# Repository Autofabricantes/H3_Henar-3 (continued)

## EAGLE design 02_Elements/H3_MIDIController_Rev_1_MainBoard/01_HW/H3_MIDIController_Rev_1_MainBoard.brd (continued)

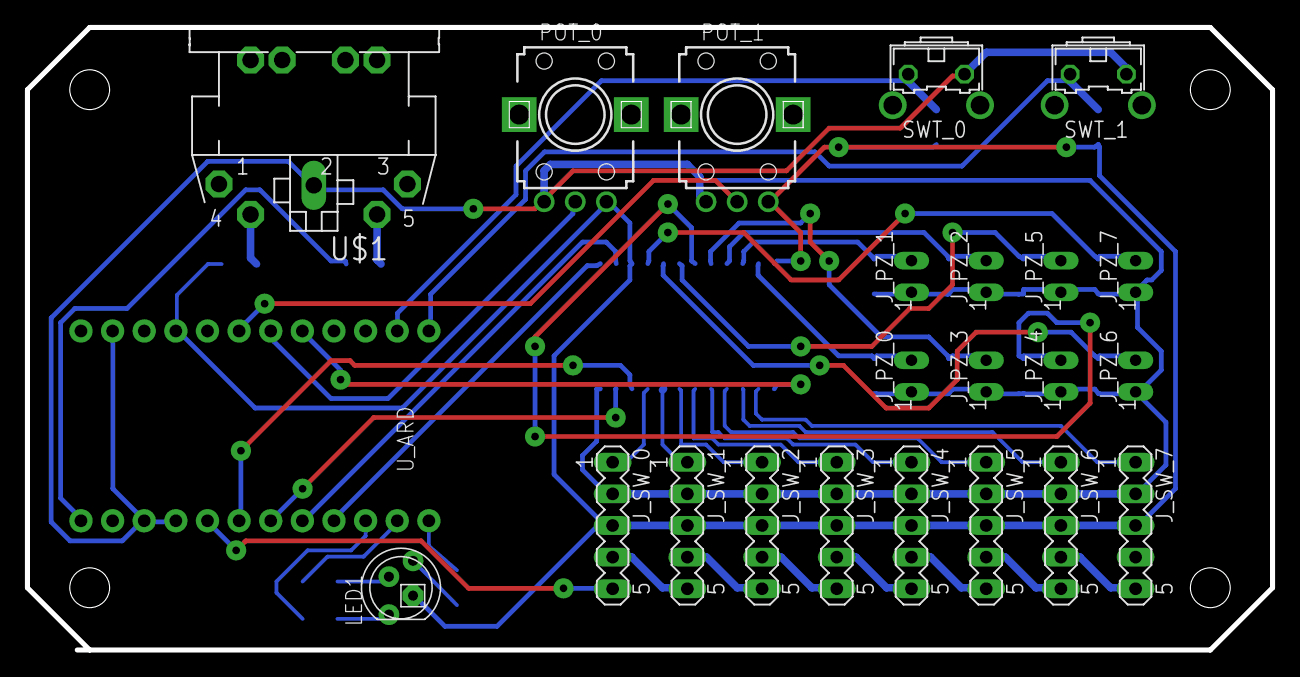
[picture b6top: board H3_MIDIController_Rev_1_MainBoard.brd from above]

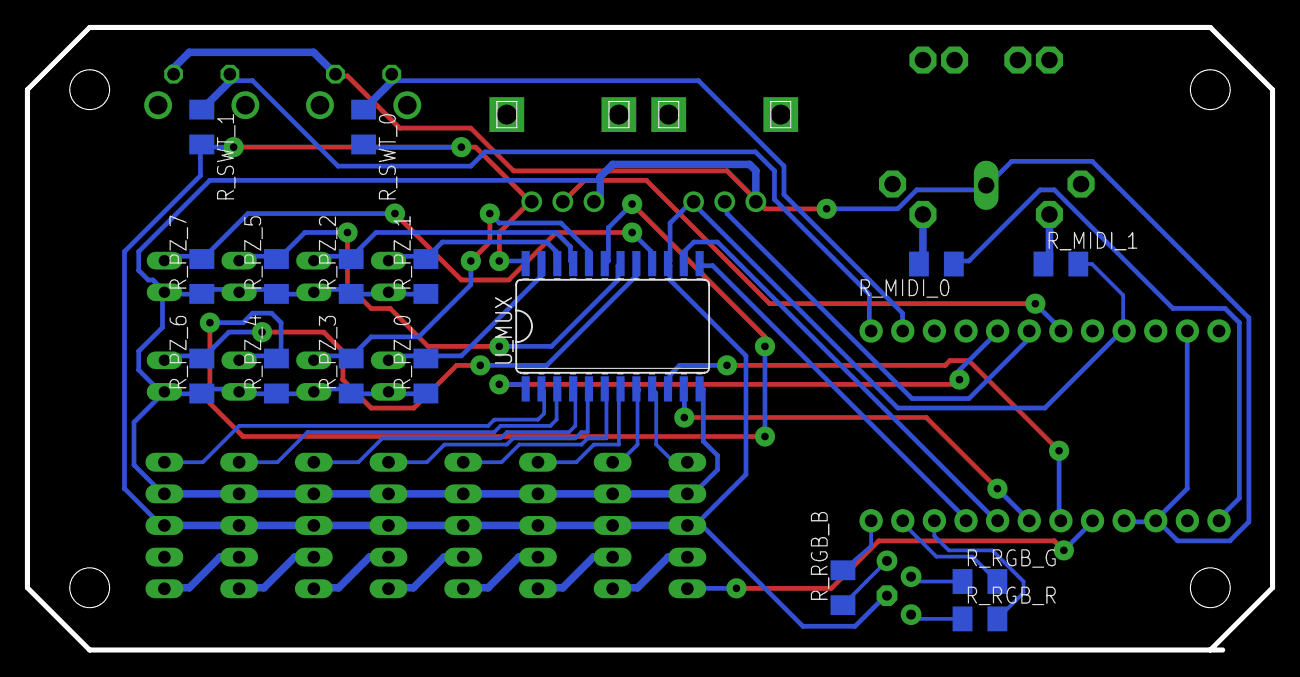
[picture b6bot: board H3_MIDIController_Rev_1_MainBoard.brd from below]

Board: 2 copper layers, 100.0 x 50.0 mm, 39 parts (16 on the bottom side), 44 nets.

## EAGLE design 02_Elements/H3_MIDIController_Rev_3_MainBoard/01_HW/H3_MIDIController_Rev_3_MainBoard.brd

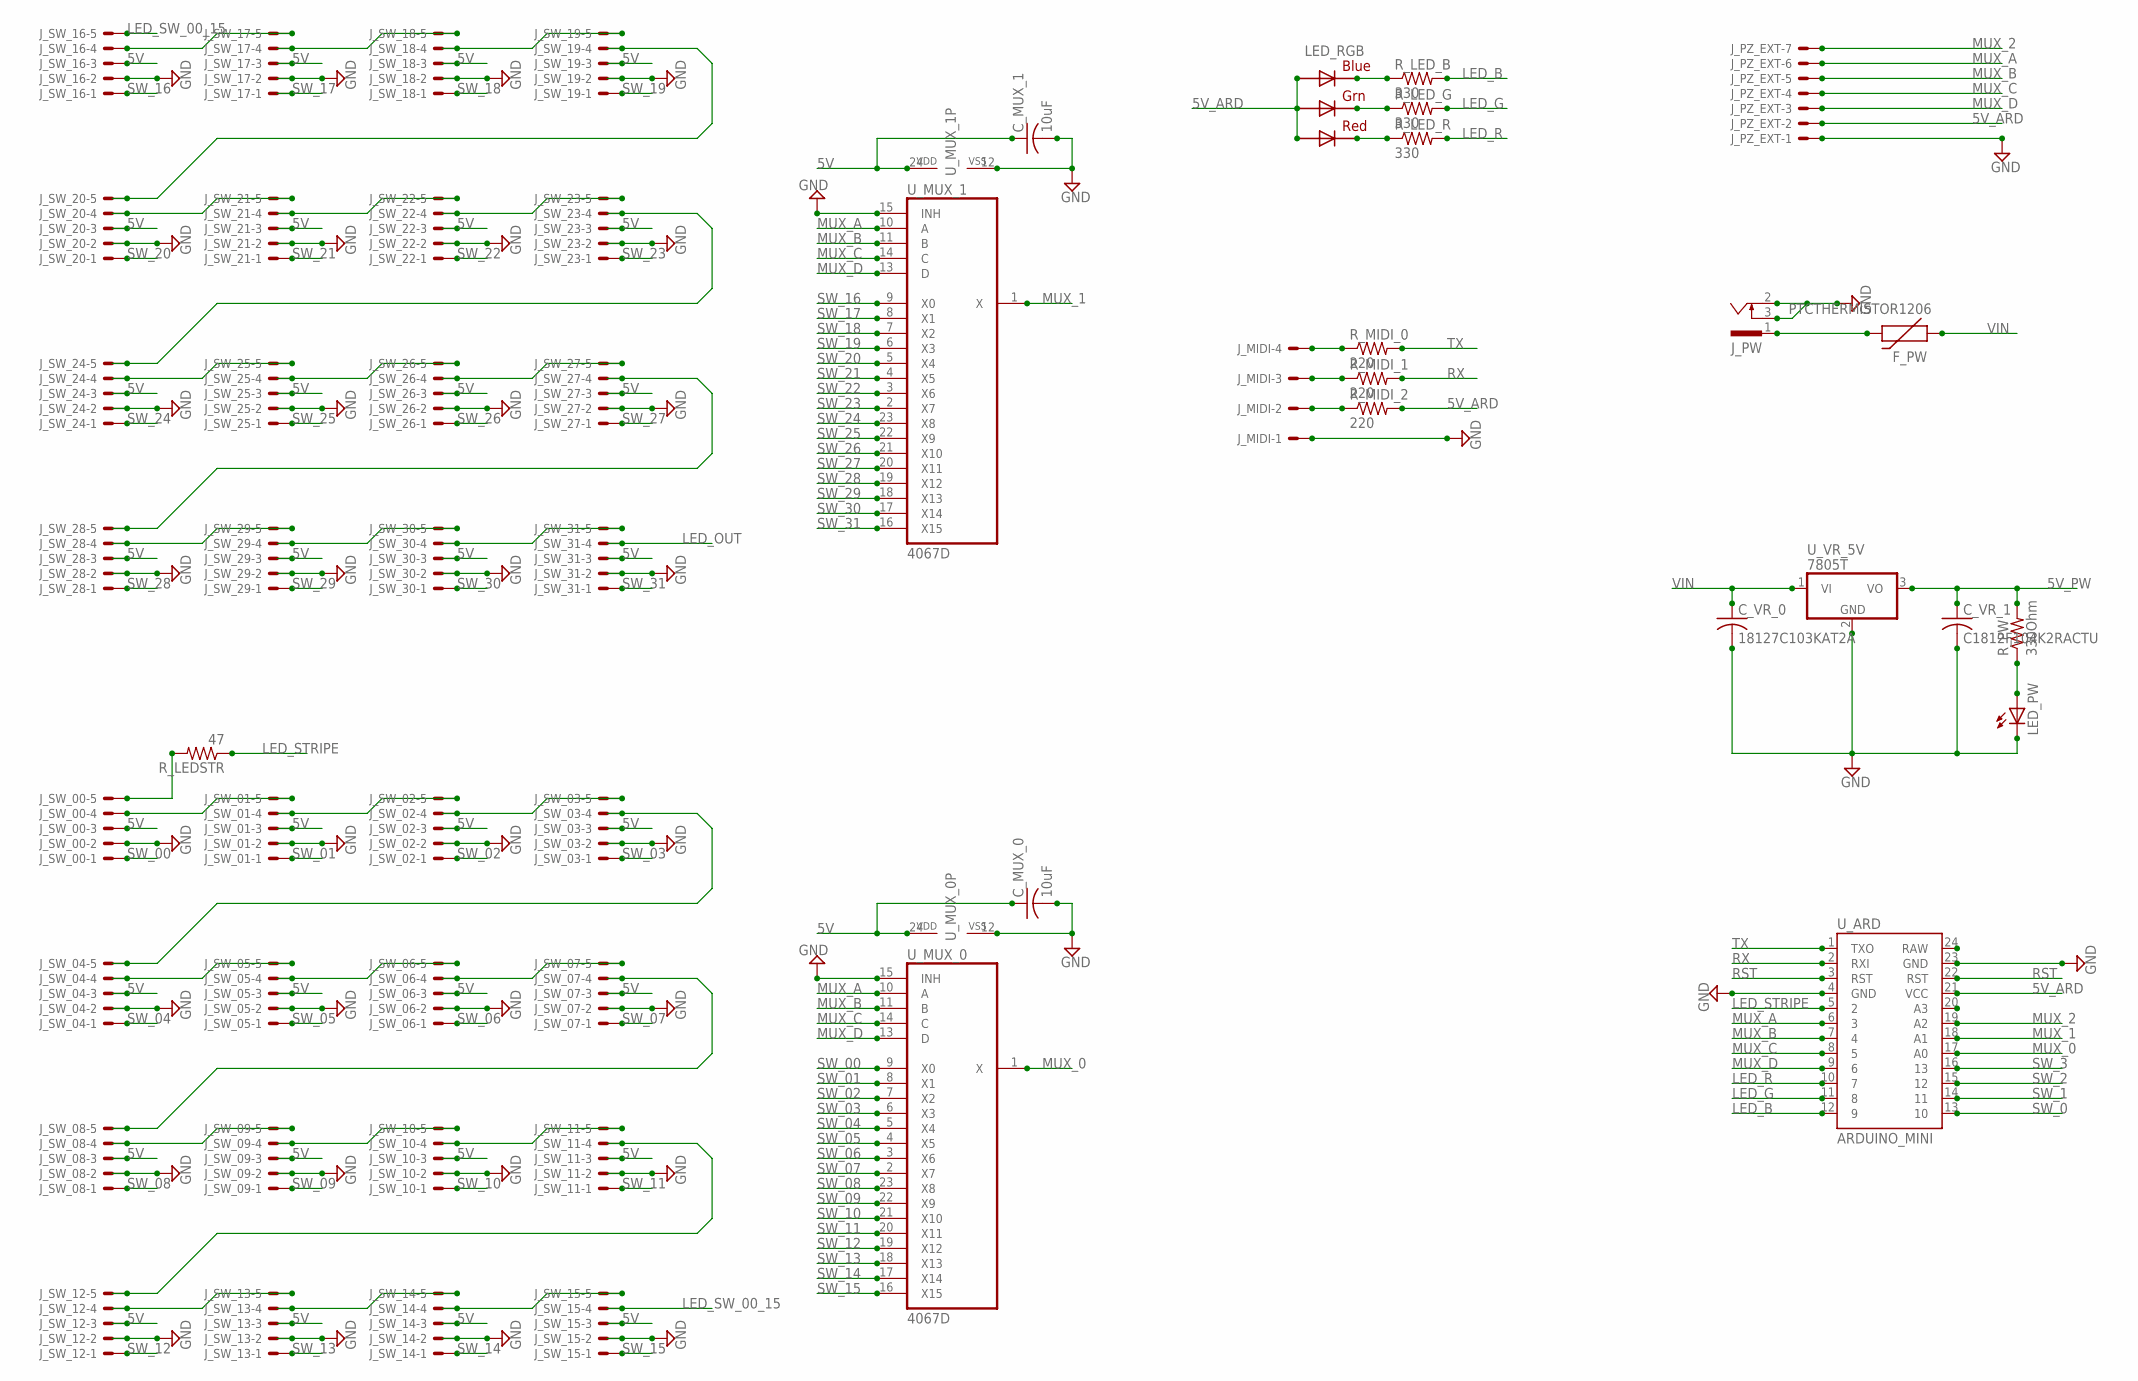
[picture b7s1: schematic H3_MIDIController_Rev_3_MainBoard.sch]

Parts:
C_MUX_0, C_MUX_1: 10uF; C1206K
C_VR_0: 18127C103KAT2A; C1812K
C_VR_1: C1812F104K2RACTU; C1812K
F_PW: PTCTHERMISTOR1206; PTC-1206
J_MIDI: 22-05-7048-04; 7395-04
J_PW: SCD-014A; SCD-014-A
J_PZ_EXT: 22-05-7078-07; 7395-07
J_SW_00, J_SW_01, J_SW_02, J_SW_03, J_SW_04, J_SW_05, J_SW_06, J_SW_07, J_SW_08, J_SW_09, J_SW_10, J_SW_11, J_SW_12, J_SW_13, J_SW_14, J_SW_15, J_SW_16, J_SW_17, J_SW_18, J_SW_19, J_SW_20, J_SW_21, J_SW_22, J_SW_23, J_SW_24, J_SW_25, J_SW_26, J_SW_27, J_SW_28, J_SW_29, J_SW_30, J_SW_31: 22-05-7058-05; 7395-05
LED_PW: LEDSMT1206; 1206
LED_RGB: RGBLED5050
R_LEDSTR: 47; M1206
R_LED_B: 330; M1206
R_LED_G: 330; M1206
R_LED_R: 330; M1206
R_MIDI_0, R_MIDI_1, R_MIDI_2: 220; M1206
R_PW: 330Ohm; M1206
U_ARD: ARDUINO_MINI
U_MUX_0, U_MUX_1: 4067D; SO24W
U_VR_5V: 7805T; TO220H

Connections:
5V: C_MUX_0.1, C_MUX_1.1, J_SW_00.3, J_SW_01.3, J_SW_02.3, J_SW_03.3, J_SW_04.3, J_SW_05.3, J_SW_06.3, J_SW_07.3, J_SW_08.3, J_SW_09.3, J_SW_10.3, J_SW_11.3, J_SW_12.3, J_SW_13.3, J_SW_14.3, J_SW_15.3, J_SW_16.3, J_SW_17.3, J_SW_18.3, J_SW_19.3, J_SW_20.3, J_SW_21.3, J_SW_22.3, J_SW_23.3, J_SW_24.3, J_SW_25.3, J_SW_26.3, J_SW_27.3, J_SW_28.3, J_SW_29.3, J_SW_30.3, J_SW_31.3, U_MUX_0.24 (VDD), U_MUX_1.24 (VDD)
5V_ARD: J_PZ_EXT.2, LED_RGB.1 (GREEN_A), LED_RGB.2 (RED_A), LED_RGB.3 (BLUE_A), R_MIDI_2.2, U_ARD.21 (VCC)
5V_PW: C_VR_1.1, R_PW.2, U_VR_5V.3 (VO)
GND: C_MUX_0.2, C_MUX_1.2, C_VR_0.2, C_VR_1.2, J_MIDI.1, J_PW.2, J_PW.3, J_PZ_EXT.1, J_SW_00.2, J_SW_01.2, J_SW_02.2, J_SW_03.2, J_SW_04.2, J_SW_05.2, J_SW_06.2, J_SW_07.2, J_SW_08.2, J_SW_09.2, J_SW_10.2, J_SW_11.2, J_SW_12.2, J_SW_13.2, J_SW_14.2, J_SW_15.2, J_SW_16.2, J_SW_17.2, J_SW_18.2, J_SW_19.2, J_SW_20.2, J_SW_21.2, J_SW_22.2, J_SW_23.2, J_SW_24.2, J_SW_25.2, J_SW_26.2, J_SW_27.2, J_SW_28.2, J_SW_29.2, J_SW_30.2, J_SW_31.2, LED_PW.C, U_ARD.4 (GND), U_ARD.23 (GND), U_MUX_0.12 (VSS), U_MUX_0.15 (INH), U_MUX_1.12 (VSS), U_MUX_1.15 (INH), U_VR_5V.2 (GND)
LED_B: R_LED_B.2, U_ARD.12 (9)
LED_G: R_LED_G.2, U_ARD.11 (8)
LED_IN1: J_SW_00.4, J_SW_01.5
LED_IN2: J_SW_01.4, J_SW_02.5
LED_IN3: J_SW_02.4, J_SW_03.5
LED_IN4: J_SW_03.4, J_SW_04.5
LED_IN5: J_SW_04.4, J_SW_05.5
LED_IN6: J_SW_05.4, J_SW_06.5
LED_IN7: J_SW_07.4, J_SW_08.5
LED_IN8: J_SW_08.4, J_SW_09.5
LED_IN9: J_SW_09.4, J_SW_10.5
LED_IN10: J_SW_10.4, J_SW_11.5
LED_IN11: J_SW_11.4, J_SW_12.5
LED_IN12: J_SW_12.4, J_SW_13.5
LED_IN13: J_SW_13.4, J_SW_14.5
LED_IN14: J_SW_14.4, J_SW_15.5
LED_IN15: J_SW_16.4, J_SW_17.5
LED_IN16: J_SW_17.4, J_SW_18.5
LED_IN17: J_SW_18.4, J_SW_19.5
LED_IN18: J_SW_19.4, J_SW_20.5
LED_IN19: J_SW_20.4, J_SW_21.5
LED_IN20: J_SW_21.4, J_SW_22.5
LED_IN21: J_SW_23.4, J_SW_24.5
LED_IN22: J_SW_24.4, J_SW_25.5
LED_IN23: J_SW_25.4, J_SW_26.5
LED_IN24: J_SW_26.4, J_SW_27.5
LED_IN25: J_SW_27.4, J_SW_28.5
LED_IN26: J_SW_28.4, J_SW_29.5
LED_IN27: J_SW_29.4, J_SW_30.5
LED_IN28: J_SW_30.4, J_SW_31.5
LED_OUT: J_SW_31.4
LED_R: R_LED_R.2, U_ARD.10 (7)
LED_STRIPE: R_LEDSTR.1, U_ARD.5 (2)
LED_SW_00_15: J_SW_15.4, J_SW_16.5
MUX_0: U_ARD.17 (A0), U_MUX_0.1 (X)
MUX_1: U_ARD.18 (A1), U_MUX_1.1 (X)
MUX_2: J_PZ_EXT.7, U_ARD.19 (A2)
MUX_A: J_PZ_EXT.6, U_ARD.6 (3), U_MUX_0.10 (A), U_MUX_1.10 (A)
MUX_B: J_PZ_EXT.5, U_ARD.7 (4), U_MUX_0.11 (B), U_MUX_1.11 (B)
MUX_C: J_PZ_EXT.4, U_ARD.8 (5), U_MUX_0.14 (C), U_MUX_1.14 (C)
MUX_D: J_PZ_EXT.3, U_ARD.9 (6), U_MUX_0.13 (D), U_MUX_1.13 (D)
unnamed: F_PW.2, J_PW.1
unnamed: J_SW_00.5, R_LEDSTR.2
unnamed: LED_PW.A, R_PW.1
unnamed: J_SW_22.4, J_SW_23.5
unnamed: LED_RGB.4 (BLUE_C), R_LED_B.1
unnamed: LED_RGB.6 (GREEN_C), R_LED_G.1
unnamed: LED_RGB.5 (RED_C), R_LED_R.1
unnamed: J_MIDI.2, R_MIDI_2.1
unnamed: J_MIDI.3, R_MIDI_1.1
unnamed: J_MIDI.4, R_MIDI_0.1
unnamed: J_SW_06.4, J_SW_07.5
RST: U_ARD.3 (RST), U_ARD.22 (RST)
RX: R_MIDI_1.2, U_ARD.2 (RXI)
SW_0: U_ARD.13 (10)
SW_00: J_SW_00.1, U_MUX_0.9 (X0)
SW_1: U_ARD.14 (11)
SW_01: J_SW_01.1, U_MUX_0.8 (X1)
SW_2: U_ARD.15 (12)
SW_02: J_SW_02.1, U_MUX_0.7 (X2)
SW_3: U_ARD.16 (13)
SW_03: J_SW_03.1, U_MUX_0.6 (X3)
SW_04: J_SW_04.1, U_MUX_0.5 (X4)
SW_05: J_SW_05.1, U_MUX_0.4 (X5)
SW_06: J_SW_06.1, U_MUX_0.3 (X6)
SW_07: J_SW_07.1, U_MUX_0.2 (X7)
SW_08: J_SW_08.1, U_MUX_0.23 (X8)
SW_09: J_SW_09.1, U_MUX_0.22 (X9)
SW_10: J_SW_10.1, U_MUX_0.21 (X10)
SW_11: J_SW_11.1, U_MUX_0.20 (X11)
SW_12: J_SW_12.1, U_MUX_0.19 (X12)
SW_13: J_SW_13.1, U_MUX_0.18 (X13)
SW_14: J_SW_14.1, U_MUX_0.17 (X14)
SW_15: J_SW_15.1, U_MUX_0.16 (X15)
SW_16: J_SW_16.1, U_MUX_1.9 (X0)
SW_17: J_SW_17.1, U_MUX_1.8 (X1)
SW_18: J_SW_18.1, U_MUX_1.7 (X2)
SW_19: J_SW_19.1, U_MUX_1.6 (X3)
SW_20: J_SW_20.1, U_MUX_1.5 (X4)
SW_21: J_SW_21.1, U_MUX_1.4 (X5)
SW_22: J_SW_22.1, U_MUX_1.3 (X6)
SW_23: J_SW_23.1, U_MUX_1.2 (X7)
SW_24: J_SW_24.1, U_MUX_1.23 (X8)
SW_25: J_SW_25.1, U_MUX_1.22 (X9)
SW_26: J_SW_26.1, U_MUX_1.21 (X10)
SW_27: J_SW_27.1, U_MUX_1.20 (X11)
SW_28: J_SW_28.1, U_MUX_1.19 (X12)
SW_29: J_SW_29.1, U_MUX_1.18 (X13)
SW_30: J_SW_30.1, U_MUX_1.17 (X14)
SW_31: J_SW_31.1, U_MUX_1.16 (X15)
TX: R_MIDI_0.2, U_ARD.1 (TXO)
VIN: C_VR_0.1, F_PW.1, U_VR_5V.1 (VI)

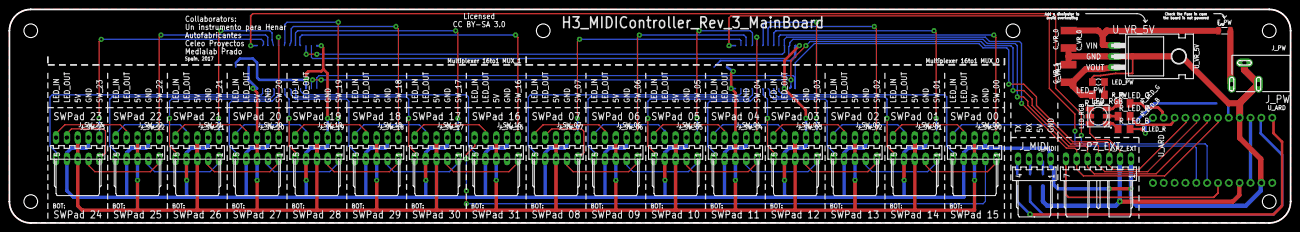
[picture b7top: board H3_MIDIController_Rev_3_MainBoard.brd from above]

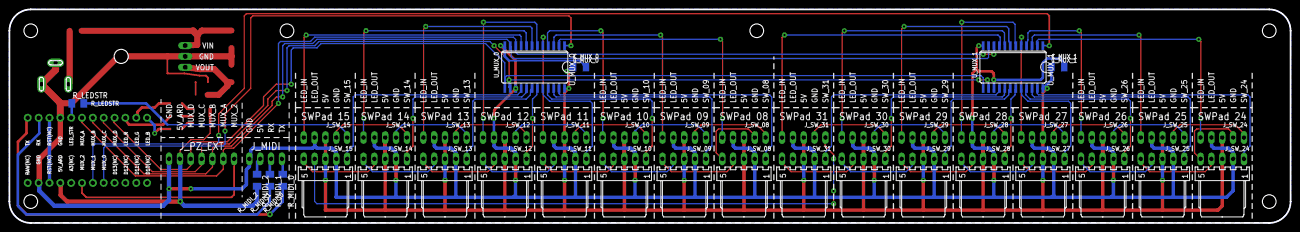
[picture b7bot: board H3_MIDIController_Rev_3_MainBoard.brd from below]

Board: 2 copper layers, 300.0 x 50.0 mm, 54 parts (24 on the bottom side), 91 nets.

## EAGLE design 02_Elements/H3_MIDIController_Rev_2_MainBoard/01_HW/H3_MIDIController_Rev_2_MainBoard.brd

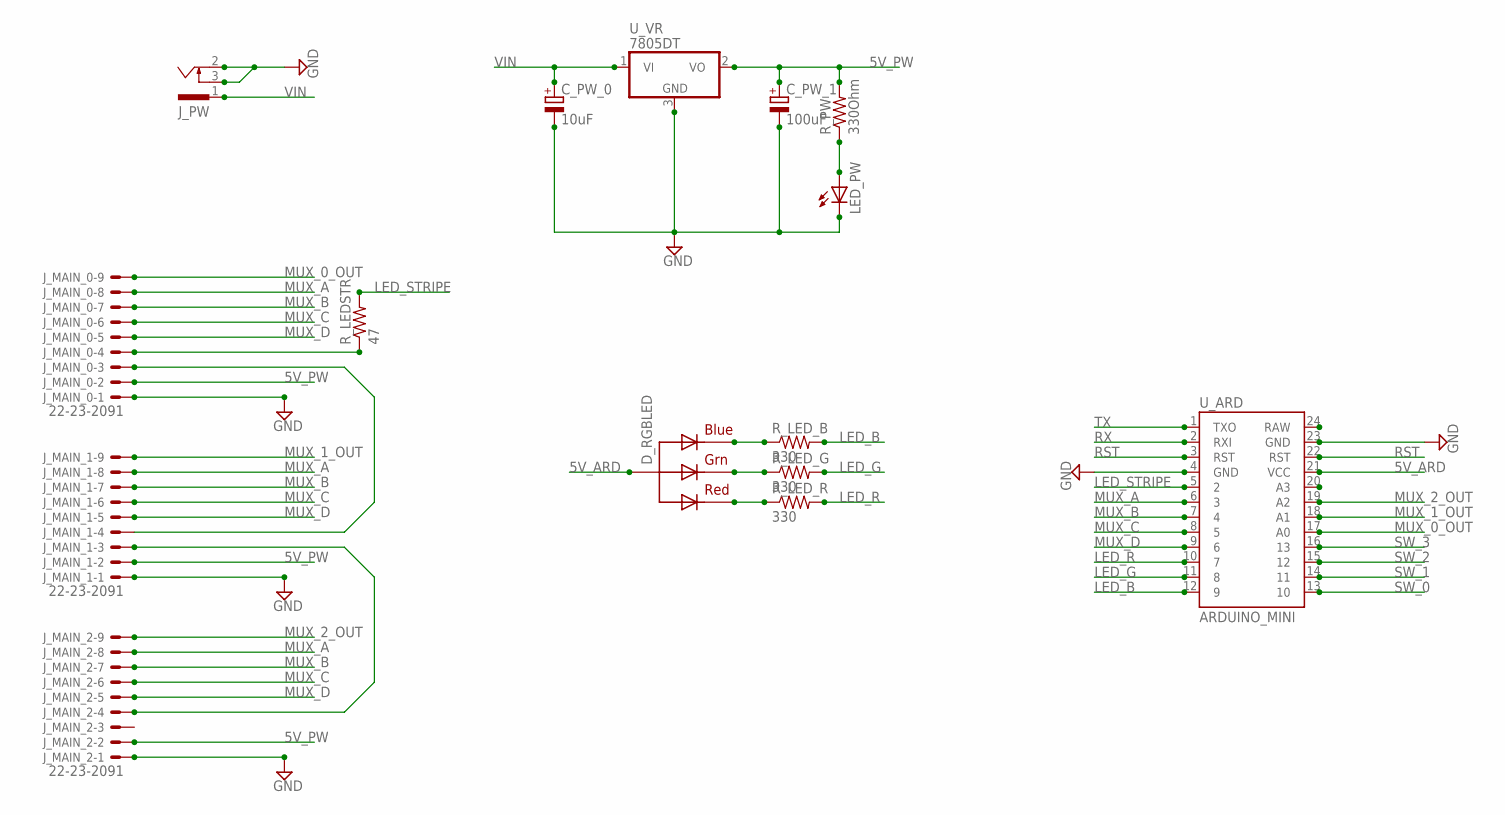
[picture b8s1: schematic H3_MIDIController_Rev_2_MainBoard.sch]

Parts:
C_PW_0: 10uF; TT2D6L
C_PW_1: 100uF; TT2D6L
D_RGBLED: RGBLED_CA-5MM; LED5MMRGB
J_MAIN_0, J_MAIN_1, J_MAIN_2: 22-23-2091
J_PW: SCD-014A; SCD-014-A
LED_PW: LEDSMT1206; 1206
R_LEDSTR: 47; M1206
R_LED_B: 330; M1206
R_LED_G: 330; M1206
R_LED_R: 330; M1206
R_PW: 330Ohm; M1206
U_ARD: ARDUINO_MINI
U_VR: 7805DT; TO252

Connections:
5V_ARD: D_RGBLED.2 (VCC), U_ARD.21 (VCC)
5V_PW: C_PW_1.+, J_MAIN_0.2, J_MAIN_1.2, J_MAIN_2.2, R_PW.2, U_VR.2 (VO)
GND: C_PW_0.-, C_PW_1.-, J_MAIN_0.1, J_MAIN_1.1, J_MAIN_2.1, J_PW.2, J_PW.3, LED_PW.C, U_ARD.4 (GND), U_ARD.23 (GND), U_VR.3 (GND)
LED_B: R_LED_B.2, U_ARD.12 (9)
LED_G: R_LED_G.2, U_ARD.11 (8)
LED_OUT: J_MAIN_0.3, J_MAIN_1.4
LED_OUT1: J_MAIN_1.3, J_MAIN_2.4
LED_R: R_LED_R.2, U_ARD.10 (7)
LED_STRIPE: R_LEDSTR.2, U_ARD.5 (2)
MUX_0_OUT: J_MAIN_0.9, U_ARD.17 (A0)
MUX_1_OUT: J_MAIN_1.9, U_ARD.18 (A1)
MUX_2_OUT: J_MAIN_2.9, U_ARD.19 (A2)
MUX_A: J_MAIN_0.8, J_MAIN_1.8, J_MAIN_2.8, U_ARD.6 (3)
MUX_B: J_MAIN_0.7, J_MAIN_1.7, J_MAIN_2.7, U_ARD.7 (4)
MUX_C: J_MAIN_0.6, J_MAIN_1.6, J_MAIN_2.6, U_ARD.8 (5)
MUX_D: J_MAIN_0.5, J_MAIN_1.5, J_MAIN_2.5, U_ARD.9 (6)
unnamed: J_MAIN_0.4, R_LEDSTR.1
unnamed: LED_PW.A, R_PW.1
unnamed: D_RGBLED.4 (BLUE), R_LED_B.1
unnamed: D_RGBLED.3 (GREEN), R_LED_G.1
unnamed: D_RGBLED.1 (RED), R_LED_R.1
RST: U_ARD.3 (RST), U_ARD.22 (RST)
RX: U_ARD.2 (RXI)
SW_0: U_ARD.13 (10)
SW_1: U_ARD.14 (11)
SW_2: U_ARD.15 (12)
SW_3: U_ARD.16 (13)
TX: U_ARD.1 (TXO)
VIN: C_PW_0.+, J_PW.1, U_VR.1 (VI)

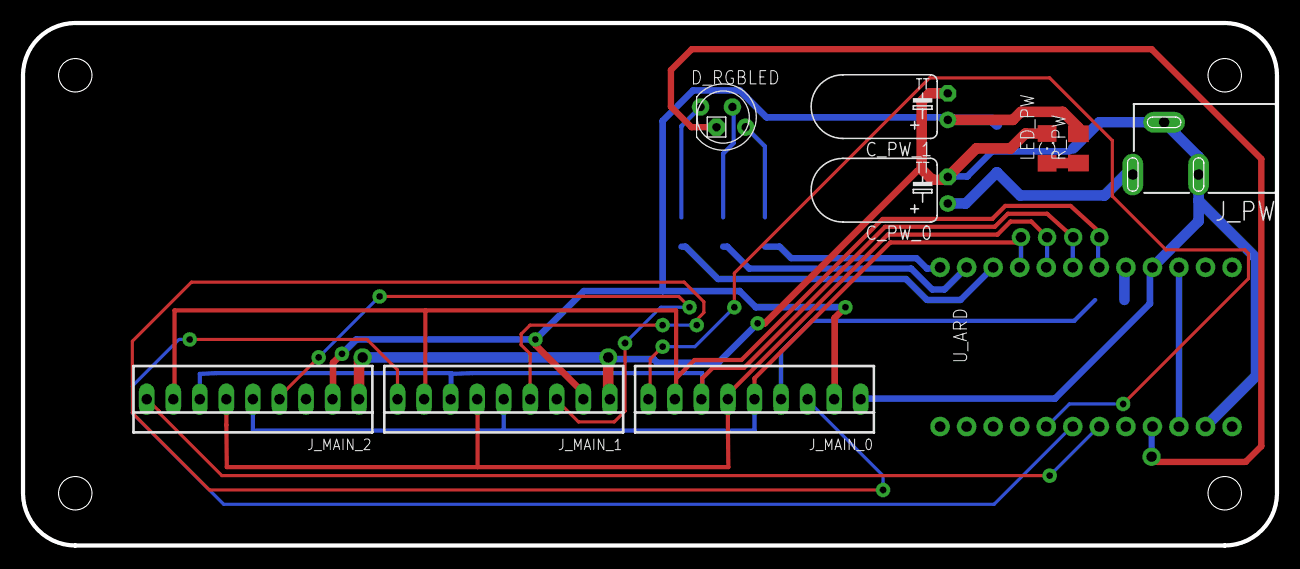
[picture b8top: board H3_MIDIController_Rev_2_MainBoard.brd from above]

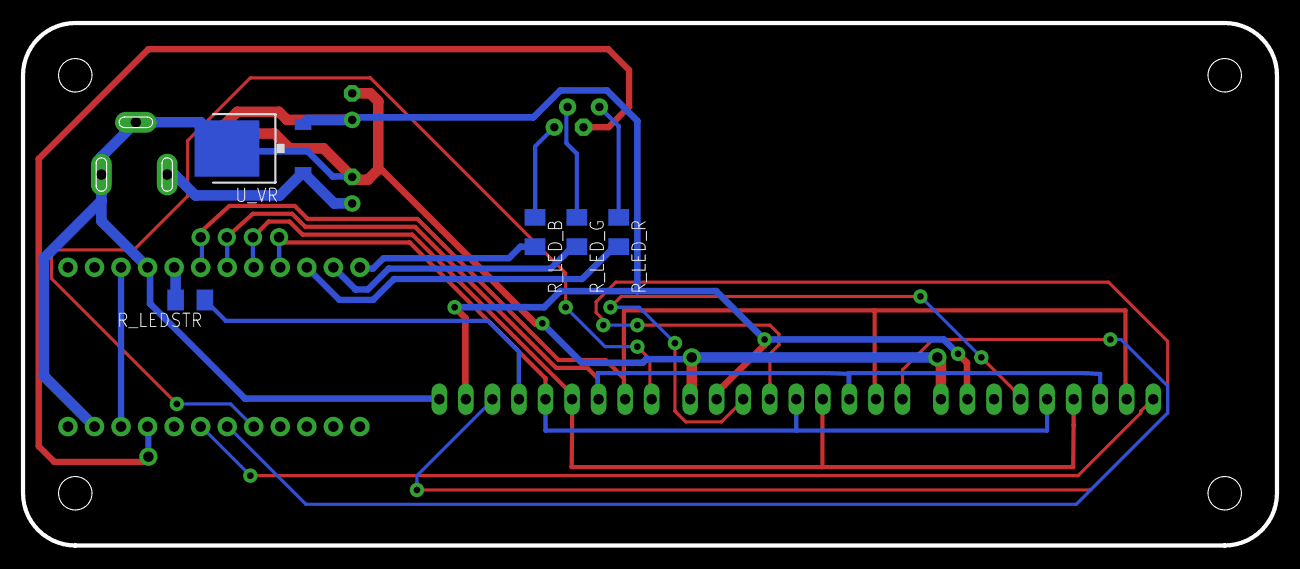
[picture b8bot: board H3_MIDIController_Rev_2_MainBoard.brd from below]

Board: 2 copper layers, 120.0 x 50.0 mm, 15 parts (5 on the bottom side), 23 nets.

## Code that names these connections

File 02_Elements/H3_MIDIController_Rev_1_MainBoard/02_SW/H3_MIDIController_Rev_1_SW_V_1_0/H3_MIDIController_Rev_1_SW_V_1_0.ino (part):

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
// Pin Definition
#define LED     2
#define MUX_A   3
#define MUX_B   4
#define MUX_C   5
#define MUX_D   6
#define LED_R   7
#define LED_G   8
#define LED_B   9
#define SWT_0   10
#define SWT_1   11
#define MUX_OUT 0
#define POT_0   1
#define POT_1   2

// Constants Definition
#define SW_Q  5     // Switch Quantity
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// Global Variables
Adafruit_NeoPixel ledPadStripe = Adafruit_NeoPixel((SW_Q*4), LED, NEO_RGB + NEO_KHZ800);

int muxSel[4] = {MUX_D,MUX_C,MUX_B,MUX_A}; // MUX Selector Pins

// Control Arrays for SW PAD
byte SW_MIDI_BYTE_1[SW_Q][2] = {{NOTE_ON,NOTE_OFF},{NOTE_ON,NOTE_OFF},{NOTE_ON,NOTE_OFF},{NOTE_ON,NOTE_OFF},{NOTE_ON,NOTE_OFF}};     // MIDI Values 1 Byte
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int PZ_THR[PZ_Q] = {PZ_THR_0, PZ_THR_1, PZ_THR_2, PZ_THR_3, PZ_THR_4, PZ_THR_5};

// Control Arrays for Potentiometers
int POT_PIN[2]={POT_0, POT_1};
int POT_MIDI[2][2]={{}};      // Pot MIDI Function and Value
int POT_TOL[2]= {5, 5};       // Variation Tolerance for Potentiometers

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  ledPadStripe.show();

  // Set Pin Modes
  pinMode(MUX_A, OUTPUT);
  pinMode(MUX_B, OUTPUT);
  pinMode(MUX_C, OUTPUT);
  pinMode(MUX_D, OUTPUT);
  pinMode(LED_R, OUTPUT);
  pinMode(LED_G, OUTPUT);
  pinMode(LED_B, OUTPUT);
  pinMode(SWT_0, INPUT);
  pinMode(SWT_1, INPUT);

}

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void SW_PAD_read(){
  for (int i=0; i < SW_Q; i++){
    for(int h=0; h<4; h++){
     digitalWrite(muxSel[h], ((i>>(3-h)) & 0x01)); //MUX Setup pin for each MUX Pin
    }
    delay(10); // Delay por MUX Setup
    if (analogRead(MUX_OUT) < SW_THR){  // If SW Pad activated
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void PZ_PAD_Read(){
  for (int i=0; i<PZ_Q; i++){
    for(int h=0; h<4; h++){
     digitalWrite(muxSel[h], (((i+8)>>(3-h)) & 0x01)); //MUX Setup pin for each MUX Pin
    }
    delay(10); // Delay por MUX Setup
    Serial.print("Channel: ");
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
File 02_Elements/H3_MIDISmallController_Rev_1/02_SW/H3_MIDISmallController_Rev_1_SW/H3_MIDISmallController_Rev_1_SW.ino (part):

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//------------------------------------------------------------------------------------------------------------------------------------------
// SW_Q                || SW_ACT                  || SW_VAR         || SW_INIT                                         || Comments
//------------------------------------------------------------------------------------------------------------------------------------------
const int SW_00_Q = 1  ;const int SW_00_ACT = 0   ;int SW_00  = 0   ;int SW_00_INIT  = 0;                      
const int SW_01_Q = 1  ;const int SW_01_ACT = 1   ;int SW_01  = 0   ;int SW_01_INIT  = SW_00_Q;               
const int SW_02_Q = 1  ;const int SW_02_ACT = 2   ;int SW_02  = 0   ;int SW_02_INIT  = (SW_00_Q + SW_01_Q);
const int SW_03_Q = 1  ;const int SW_03_ACT = 3   ;int SW_03  = 0   ;int SW_03_INIT  = (SW_00_Q + SW_01_Q + SW_02_Q);


//------------------------------------------------------------------------------------------------------------------------------------------
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// -----------------------------------------------------------------------------------------------------------------------------------------
// Pin Definition
const int LED          =   2;
const int MUX_A        =   3;
const int MUX_B        =   4;
const int MUX_C        =   5;
const int MUX_D        =   6;
const int MUX_0        =   0;
const int JOY_SW       =   7;
const int JOY_X        =   2;
const int JOY_Y        =   1;
// Constant Values Definition
const bool ON          =   1;         // General ON value
const bool OFF         =   0;         // General OFF value
int        muxSel[4] = {MUX_D, MUX_C, MUX_B, MUX_A}; // MUX Selector Pins
const int  MAX_MIDI_VEL = 127;
// MIDI Global Variables
int       GEN_OCT = 3;     // Global OCTAVE (Make sure initial value is within MIN and MAX)
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  ledPadStripe.show();

  // Set Pin Modes
  pinMode(MUX_A, OUTPUT);
  pinMode(MUX_B, OUTPUT);
  pinMode(MUX_C, OUTPUT);
  pinMode(MUX_D, OUTPUT);
  pinMode(JOY_SW, INPUT);

  // Control Arrays Initialization
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
void SET_MUXGATE(int GATENUM){
  for (int h = 0; h < 4; h++) {
      digitalWrite(muxSel[h], ((GATENUM >> (3 - h)) & 0x01)); //MUX Setup pin for each MUX Pin
  }
  delay(5); // Delay por MUX Setup
}
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
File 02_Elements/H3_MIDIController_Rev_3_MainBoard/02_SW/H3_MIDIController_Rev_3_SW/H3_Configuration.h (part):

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// ---------------------------------------------------H3 Pin Definition---------------------------------------------------------------------
// -----------------------------------------------------------------------------------------------------------------------------------------
const int LED                 =   2;
const int MUX_A               =   3;
const int MUX_B               =   4;
const int MUX_C               =   5;
const int MUX_D               =   6;
const int MUX_0               =   A0;
const int MUX_1               =   A1;
const int MUX_2               =   A2;

// -----------------------------------------------------------------------------------------------------------------------------------------
// ---------------------------------------------------Control and Configuration values Definition-------------------------------------------
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// Constant Values Definition
const bool ON                 =   1;         // General ON value
const bool OFF                =   0;         // General OFF value
const int muxSel[4]           =   {MUX_D, MUX_C, MUX_B, MUX_A}; // MUX Selector Pins MUX_D, MUX_C, MUX_B, MUX_A
const int MAX_MIDI_VEL        = 127;
const int SW_ITE              =   0;
const int SW_ITE_MAX          =   5;
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const int MAX_MENU            =   3; // Menu Mode Flag (Values 0, 1)
const int FADESTEPS_C         =   5; // GENERAL FadeSteps
const int FADEDELAY_C         =   5; // GENERAL FadeDelay
const int MUX_SETUP_DELAY     =   7; // Mux Delay for PZPad
const int PZ_MEASURE_CYCLE    =   3;
const int PZ_AUTOCAL_CYCLES   =  30;
const int PZ_GEN_THR          =   3;
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
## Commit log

2017-12-14 First version of README.md
    Provisional, fast version. Needs links.
2017-12-24 Element Upload 00
    First upload of Element Files of the project, copied from the shared folders in Google Drive.
2018-01-04 General Upload
    Upload fo several items. Part of initial Setup
2018-01-16 Project Update
    Upload of several documentation elements.
2018-01-23 More uploads
    Upload of old elements, as part of the repository Setup
2018-01-25 Documentation Upload
    Upload of generate diagrams, reshaped logos and general images.
2018-01-29 update Readme.md
    Sync with Wiki Home Page
2018-07-09 SW Updated
    Added SW_Pad, PZ_Pad, Col, SW_Col as struct.
    First approach to PZ_Pad signal filtering (IIR SW Filter)
2018-07-14 SW Update
    Added:
    - Init LED Sequence
    - PZ Autocalibration and better performance
    Eyh nobody but me reads this :'(
2018-07-15 SW Update
    Added separated H3_Configuration.h containing all the constant and struct definitions
2018-07-16 SW Update
    Added some new features to be expanded later.
2018-07-22 SW Update -> No PZ_Pads anymore
    This code replaces the PZ_Pads for SW_Pads following the design change due to the 50Hz noise in the Piezos.
2018-08-01 SW Update
    Changes in the struct of SWPad.
    Minor changes in LED management.
2018-08-02 SW Update
    Added:
    - Reset Feaure
    - Switch ON timer
    - Instrument selection at init
    - Variety of Aux functions
2018-08-04 SW Update
    Added Menu mode and other minor features
2018-08-05 SW Update
    Added Features:
    - EEPROM Save
    - Factory Reset
    - Menu0, Menu1 complete features
2018-08-06 SW Release
    Code for the first Tests
2018-08-06 Docu Update
    Poster Guide. Needs improvement but I'm so busy. I should perhaps have a more relaxed life and accept the time limitations of the modern world. That may make me way happier
2018-10-22 Simple Update
    Added images and Reduced_00. It is Ok it is just me reading this noone really cares.
2018-10-29 Reduced_00 First Operational
    Uploaded First Operational SW of the Reduced_00 version, needs testing in real HW
2018-11-05 Updated Reduced_00
    Fixed Reduced_00 reported problems
2018-11-05 Update 02_Elements/H3_MIDIController_Rev_3_MainBoard/02_SW/H3_MIDIController_Rev_3_SW_Reduced_00/H3_MIDIController_Rev_3_SW_Reduced_00.ino
    This is it
2018-11-10 Reduced Fix
    Fixed Row of MODE (CD2 to CD)
2018-11-10 Reduced Fix
    Another Fix of the Reduced Mode
2018-11-13 Created Ableton Configuration Folder
    Added folder for Ableton configurations
2019-10-22 Added Velostat Test
    Added small circuit and Arduino Code to test the Velostat new Pads
2021-11-18 Minor fix (paragraphs 07, 09, 19, 57)
2022-04-07 Denomination fixed (line 11)
    - minor proposal (paragraph 19)
